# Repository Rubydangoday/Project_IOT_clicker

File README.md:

# Project_IOT_clicker — Hệ thống phản hồi lớp học dùng Remote nRF52840 (ARS)

Báo cáo môn học **IoT (IOTS337929)**, Nhóm 2, 
**ARS (Audience Response System)** là hệ thống hỏi–đáp trên lớp:
- Mỗi học sinh có một **Remote nRF52840** do nhóm tự thiết kế mạch.
- **Laptop giáo viên** vừa là máy chủ, vừa dùng Bluetooth sẵn có để thu đáp án, không cần thiết bị trung gian.
- Kết quả hiện ngay trên bảng điều khiển và màn chiếu, đồng thời được lưu lại để học sinh và phụ huynh xem trên web.
- Một **máy chủ Cloud 24/24** được laptop tự đồng bộ, để học sinh và phụ huynh dùng ở nhà.

📄 Báo cáo đầy đủ: [docs/bao-cao/Bao_cao_IOT_nhom2.docx](docs/bao-cao/Bao_cao_IOT_nhom2.docx)

---

## Cấu trúc thư mục

```
Project_IOT_clicker/
├── hardware/          Mạch Remote: dự án KiCad (sơ đồ nguyên lý, PCB 2 lớp 68×80 mm, thư viện ký hiệu/footprint,
│   ├── kicad/         Gerber prototype), bảng linh kiện BOM, ảnh sơ đồ và mạch in
│   ├── images/
│   └── BOM_linhkien_nhom2.xlsx
├── firmware/          Firmware Remote nRF52840 (Arduino, Adafruit nRF52 core 1.7.0)
│   └── ARS_remote_v3_17/   ← bản đang dùng (BLE advertising A6, LE 1M); các thư mục khác là phiên bản cũ / dự phòng GATT
├── server/            Phần mềm máy chủ phía Bluetooth (Python 3)
│   ├── bridge/        Bộ thu Bluetooth: ble_adv.py (đang dùng), adv_protocol.py, adv_phy.py (LE 1M); ble_gatt.py, ble_scan.py, bridge.py (dự phòng)
│   ├── ingest/        Bộ xử lý gói: ingest_adv.py (đang dùng), ingest.py (luật nghiệp vụ)
│   ├── common/        Đọc cấu hình, kết nối CSDL
│   └── history/       Bộ thu các phiên bản cũ
├── database/          MariaDB: schema.sql + migration 002–017
├── web/               Ứng dụng web PHP 8: cổng giáo viên, học sinh, phụ huynh, quản trị; API JSON; đồng bộ Cloud
├── deploy/            Cài đặt Ubuntu (install_ubuntu.sh, --cloud), dịch vụ systemd, nâng cấp/hoàn tác V3.16→V3.18, lệnh `ars`
├── tests/             Kiểm thử web (830 kiểm tra), giao thức quảng bá, LE 1M, firmware chạy giả lập trên máy tính
├── tools/             Đo 100 lần gửi, đo độ trễ, phân tích trace HCI, giả lập nhiều Remote
├── docs/              Tài liệu
│   ├── bao-cao/       Báo cáo môn học (Word)
│   ├── huong-dan-su-dung/  Hướng dẫn cho giáo viên, học sinh, phụ huynh, lập trình viên
│   ├── phien-ban/     Ghi chú từng phiên bản (START_HERE_*, UPGRADE_*, CHANGES_*), báo cáo hợp nhất V3.18 + Cloud
│   ├── HUONG_DAN_CAI_DAT.md · HUONG_DAN_CLOUD.md · HUONG_DAN_NGUOI_MOI.md · TONG_HOP_DU_AN.md
│   ├── KY_THUAT_CHI_TIET.md   Kiến trúc, luồng dữ liệu, giao thức (chi tiết kỹ thuật)
│   └── GATT_PROTOCOL_V3_11.md · BLUEZ_REQUIRED_CONFIG.md · ARS_BLE_Project_Handover.md
├── samples/           Đề thi mẫu (5 bộ × 20 câu: CSV/XLSX/DOCX), file mẫu nhập liệu
└── config.ini.example Cấu hình mẫu (DB, MQTT, Bluetooth)
```

## Kiến trúc

```
 TRÊN LỚP (laptop giáo viên, chạy offline)                                         Ở NHÀ (24/24)
 ┌──────────┐ BLE advertising ┌────────────────┐  MQTT  ┌────────────────┐  SQL  ┌─────────┐   tự đồng bộ   ┌───────────┐
 │ Remote   │ A6, LE 1M ─────▶│ Bộ thu BLE     │──────▶│ Bộ xử lý gói    │──────▶│ MariaDB │──── 3 phút ───▶│ ARS Cloud │◀── học sinh,
 │ nRF52840 │◀── STATE, KẾT QUẢ│ ble_adv.py     │◀──────│ ingest_adv.py   │◀──────│         │   (HTTPS JSON)  │ (Oracle + │    phụ huynh
 └──────────┘   (token 64 bit)└────────────────┘ Mosquitto└────────────────┘       └────▲────┘                 │ Tailscale)│
                                                                                       │                      └───────────┘
                                                              Web PHP (Apache) ────────┘ ◀── giáo viên, màn chiếu, học sinh, phụ huynh
```

Remote và bộ thu **chỉ truyền/nhận**. Mọi kiểm tra hợp lệ nằm ở bộ xử lý gói, nên muốn đổi luật chỉ cần sửa máy chủ, không phải nạp lại hàng chục Remote.

## Phần cứng Remote

Mạch 2 lớp 68×80 mm thiết kế bằng KiCad, gồm module nRF52840 SuperMini, bàn phím ma trận 14 phím, LED 7 đoạn 2 chữ số, đèn đỏ/xanh và nguồn 2 pin AA. File gốc nằm trong [hardware/kicad/](hardware/kicad/), Gerber trong [hardware/kicad/gerber_prototype/](hardware/kicad/gerber_prototype/), danh sách linh kiện trong [hardware/BOM_linhkien_nhom2.xlsx](hardware/BOM_linhkien_nhom2.xlsx).

**Sơ đồ nguyên lý**

| PCB mặt trên | PCB mặt dưới |
|:---:|:---:|
|  |  |

**Mạch thật đã lắp ráp** (Remote chạy bằng 2 pin AA, LED 7 đoạn đang hiển thị)

| | |
|:---:|:---:|
|  |  |

## Tính năng chính

| Khối | Tính năng |
|---|---|
| **Phần cứng** | Bo 2 lớp 68×80 mm; bàn phím ma trận 14 phím; LED 7 đoạn 2 số; đèn đỏ/xanh; 2 pin AA qua tăng áp, MOSFET chống ngược cực. Chi phí linh kiện ≈ 217.000 đ/Remote |
| **Firmware V3.17** | Nhập room/ID; điểm danh; chọn đáp án A–J; tự theo câu giáo viên đang chiếu, khoá khi câu đóng; tắt LED sau 30 giây; mỗi lần gửi là một giao dịch có token, gửi lại tối đa 6 lần |
| **Truyền không dây** | BLE advertising không kết nối (gói A6 21 byte), STATE/KẾT QUẢ ngược lại; laptop tắt Coded PHY để dùng LE 1M; đo 1 Remote: trung vị 597 ms, p95 1,17 s |
| **Máy chủ** | 10 bước kiểm tra kèm mã lý do từ chối; lưu kết quả giao dịch cùng đáp án trong một giao dịch CSDL (gửi lại không ghi trùng); tự đóng câu hết giờ |
| **Web giáo viên** | Lớp và danh sách học sinh (nhập Excel/CSV/Word/TXT); soạn câu từ Word/Excel/PDF/PowerPoint, công thức toán, trộn đề; bảng điều khiển và màn chiếu thời gian thực; **điểm danh tự động**; kết quả theo câu (p, D) và học sinh; xuất Excel/CSV; bài giảng; bài tập về nhà (AI gợi ý chấm); thi đua; **cấp tài khoản phụ huynh theo SĐT** |
| **Web học sinh** | Đăng nhập MSSV; ôn tập, sổ câu sai; bài tập về nhà (tệp, ảnh, ghi âm); bài giảng; thi đua; trợ lý học tập AI |
| **Web phụ huynh** | Đăng nhập bằng SĐT (bắt buộc đổi mật khẩu lần đầu) hoặc mã mời; **thông báo điểm danh và điểm sau mỗi buổi**; chuyên cần, tiến độ, kiến thức còn yếu, nhận xét |
| **Quản trị** | Giáo viên đăng ký trước, nhập mã mời sau (quản trị viên duyệt); trường và lớp hành chính; cấu hình AI, Zalo/SMS |
| **Cloud** | Máy chủ 24/24 (Oracle Cloud Always Free + Tailscale Funnel); laptop tự đồng bộ một chiều mỗi 3 phút, thử lại khi mất mạng |

## Công nghệ

- **Phần cứng:** nRF52840 SuperMini (ARM Cortex-M4F, BLE 5.0), KiCad.
- **Firmware:** Arduino C++, Adafruit nRF52 core (Bluefruit), SoftDevice, FreeRTOS.
- **Sóng:** BLE advertising, LE 1M PHY.
- **Bộ thu:** Python 3, bleak, dbus-fast, BlueZ / D-Bus, Bluetooth MGMT API.
- **Truyền tin nội bộ:** MQTT (Mosquitto, paho-mqtt, MQTT qua WebSocket).
- **CSDL:** MariaDB (InnoDB, VIEW).
- **Web:** PHP 8 (không framework), Apache, JavaScript thuần, KaTeX, mã QR, xuất Excel/Word, đọc PDF (poppler).
- **AI:** Anthropic Claude, Google Gemini, OpenAI, có chế độ Cơ bản không cần Internet.
- **Đăng nhập:** OAuth 2.0 Google.
- **Cloud và vận hành:** Oracle Cloud, Tailscale Funnel, Avahi mDNS, systemd, Ubuntu.
- **Kiểm thử:** Python unittest, requests, BeautifulSoup, g++.

## Cài đặt nhanh

**Laptop lớp học mới (Ubuntu 22.04 / 24.04)**
```bash
sudo bash deploy/install_ubuntu.sh                 # web, CSDL, MQTT, dịch vụ; mở http://ars.local/gv
# chuyển sang truyền quảng bá V3.18 (theo thứ tự, mỗi bước có sao lưu + hoàn tác):
sudo bash deploy/install_gatt.sh && sudo bash deploy/install_adv16.sh
sudo bash deploy/update_adv17.sh && sudo bash deploy/update_adv18.sh
```
Nạp firmware `firmware/ARS_remote_v3_17/ARS_remote_v3_17.ino` cho Remote (Arduino IDE, board Adafruit nRF52).

**Máy chủ Cloud** (Ubuntu, không cần Bluetooth): `sudo bash deploy/install_ubuntu.sh --cloud`, sau đó làm theo [docs/HUONG_DAN_CLOUD.md](docs/HUONG_DAN_CLOUD.md).

Hướng dẫn sử dụng: [docs/huong-dan-su-dung/](docs/huong-dan-su-dung/README.md) · Cài đặt chi tiết: [docs/HUONG_DAN_CAI_DAT.md](docs/HUONG_DAN_CAI_DAT.md) · Kỹ thuật: [docs/KY_THUAT_CHI_TIET.md](docs/KY_THUAT_CHI_TIET.md)

## Kiểm thử

| Hạng mục | Lệnh | Kết quả |
|---|---|---|
| Web, CSDL, đồng bộ Cloud (11 bộ, CSDL MariaDB tạm) | `bash tests/run_local.sh` | 830/830 đạt, 0 cảnh báo PHP |
| Giao thức quảng bá, bộ thu, bộ xử lý gói | `python3 tests/adv_unit.py` | 19/19 đạt |
| Cấu hình LE 1M, trace HCI | `python3 tests/adv18_unit.py` | 11/11 đạt |
| Firmware chạy giả lập trên máy tính | `bash tests/adv_firmware_host/run.sh` | Đạt |
| Remote thật trên PCB, LE 1M | `bash tools/test_adv18_100.sh` | 34/34 giao dịch có kết quả; trung vị 597 ms, p95 1.172 ms |

Giới hạn: mới đo thực tế với **một** Remote; tải vô tuyến khi cả lớp (khoảng 50 Remote) bấm cùng lúc chưa được đo.

## Nhóm thực hiện (Nhóm 2)

| Họ và tên | MSSV |
|---|---|
| Nguyễn Thị Ánh Ngọc | 23134040 |
| Lê Lữ Anh Khôi | 23134033 |
| Trần Trăng Sáng | 23134050 |
| Nguyễn Trung Tín | 23134055 |

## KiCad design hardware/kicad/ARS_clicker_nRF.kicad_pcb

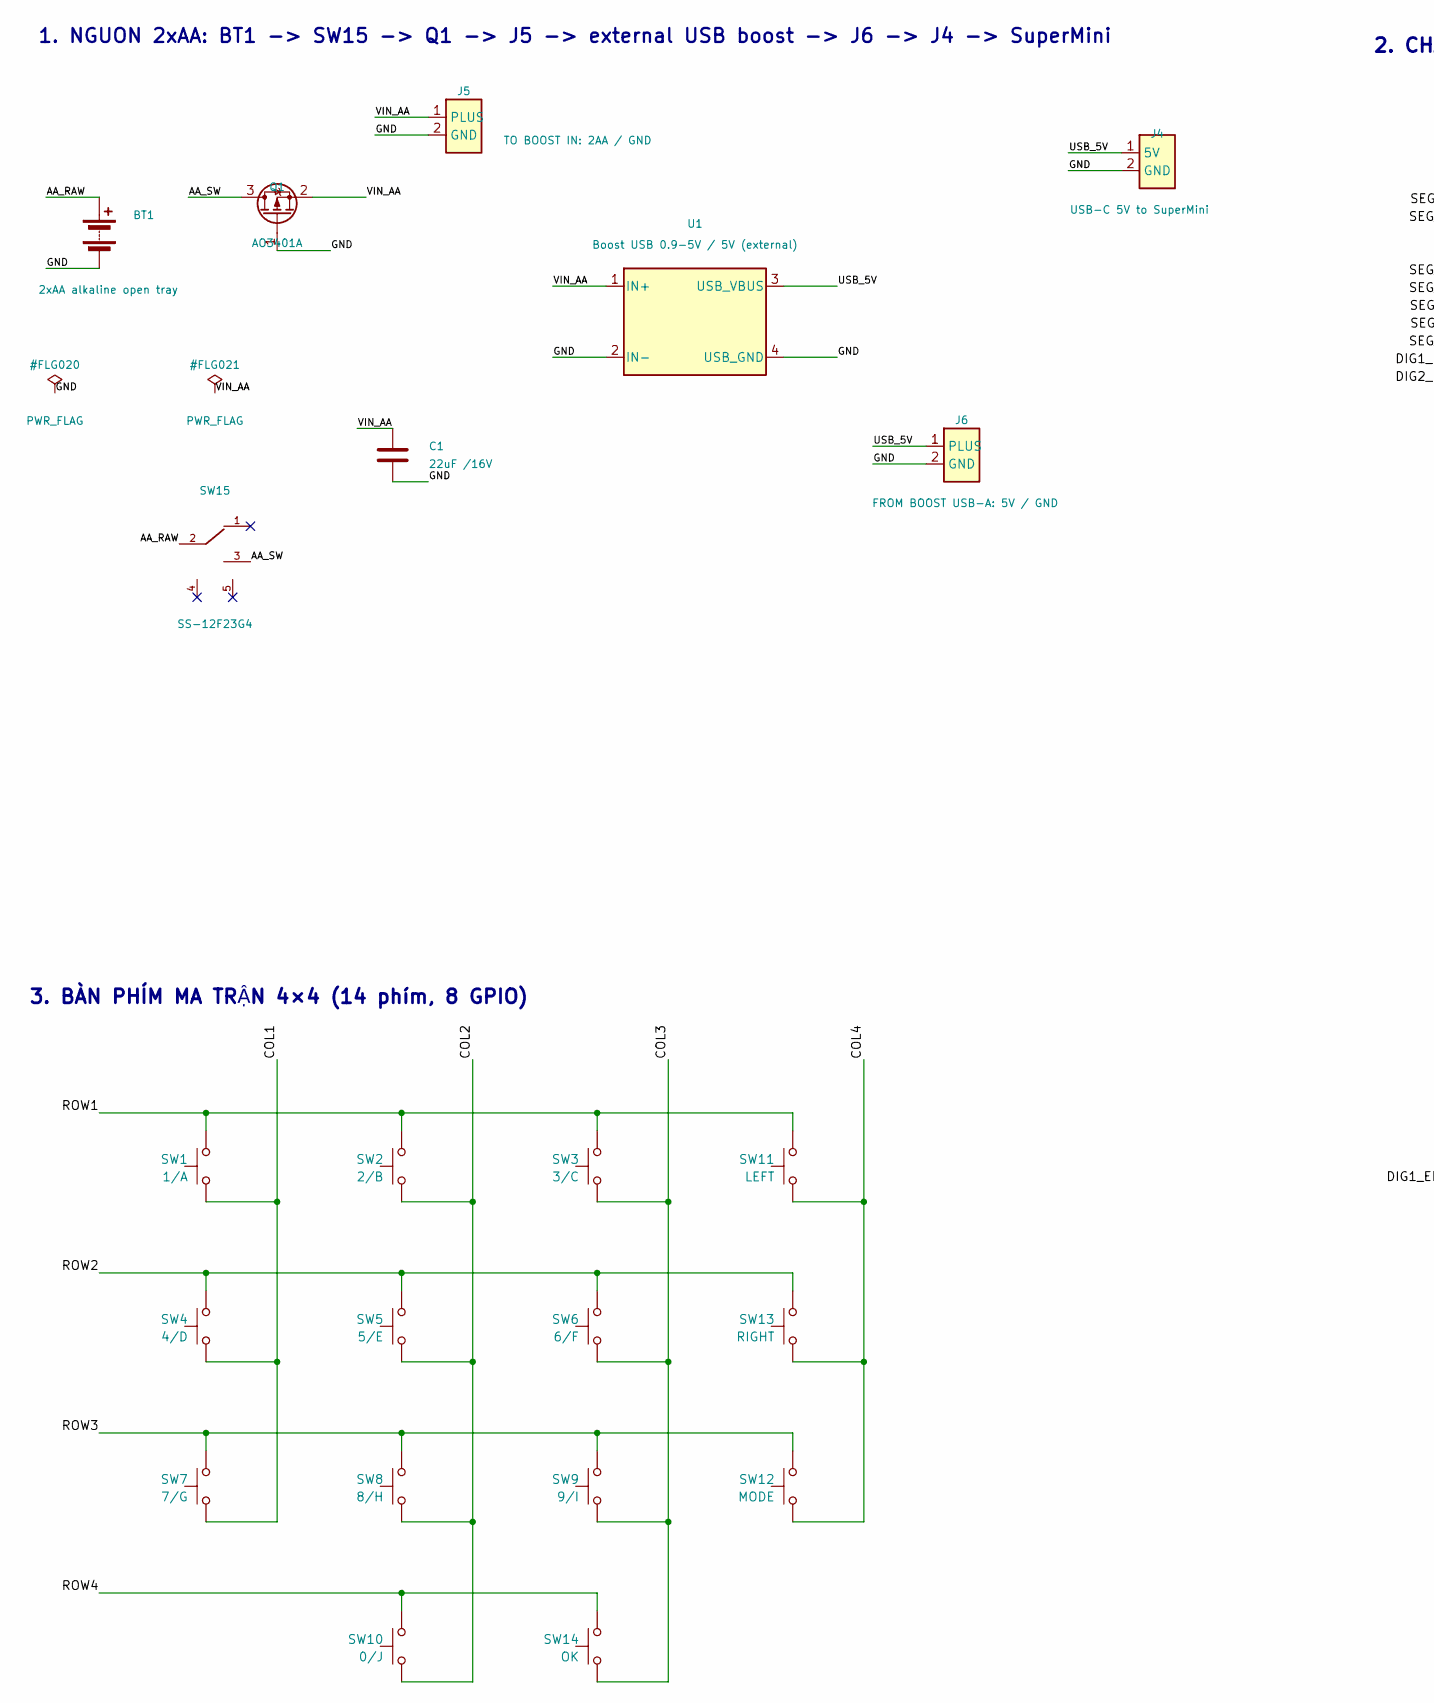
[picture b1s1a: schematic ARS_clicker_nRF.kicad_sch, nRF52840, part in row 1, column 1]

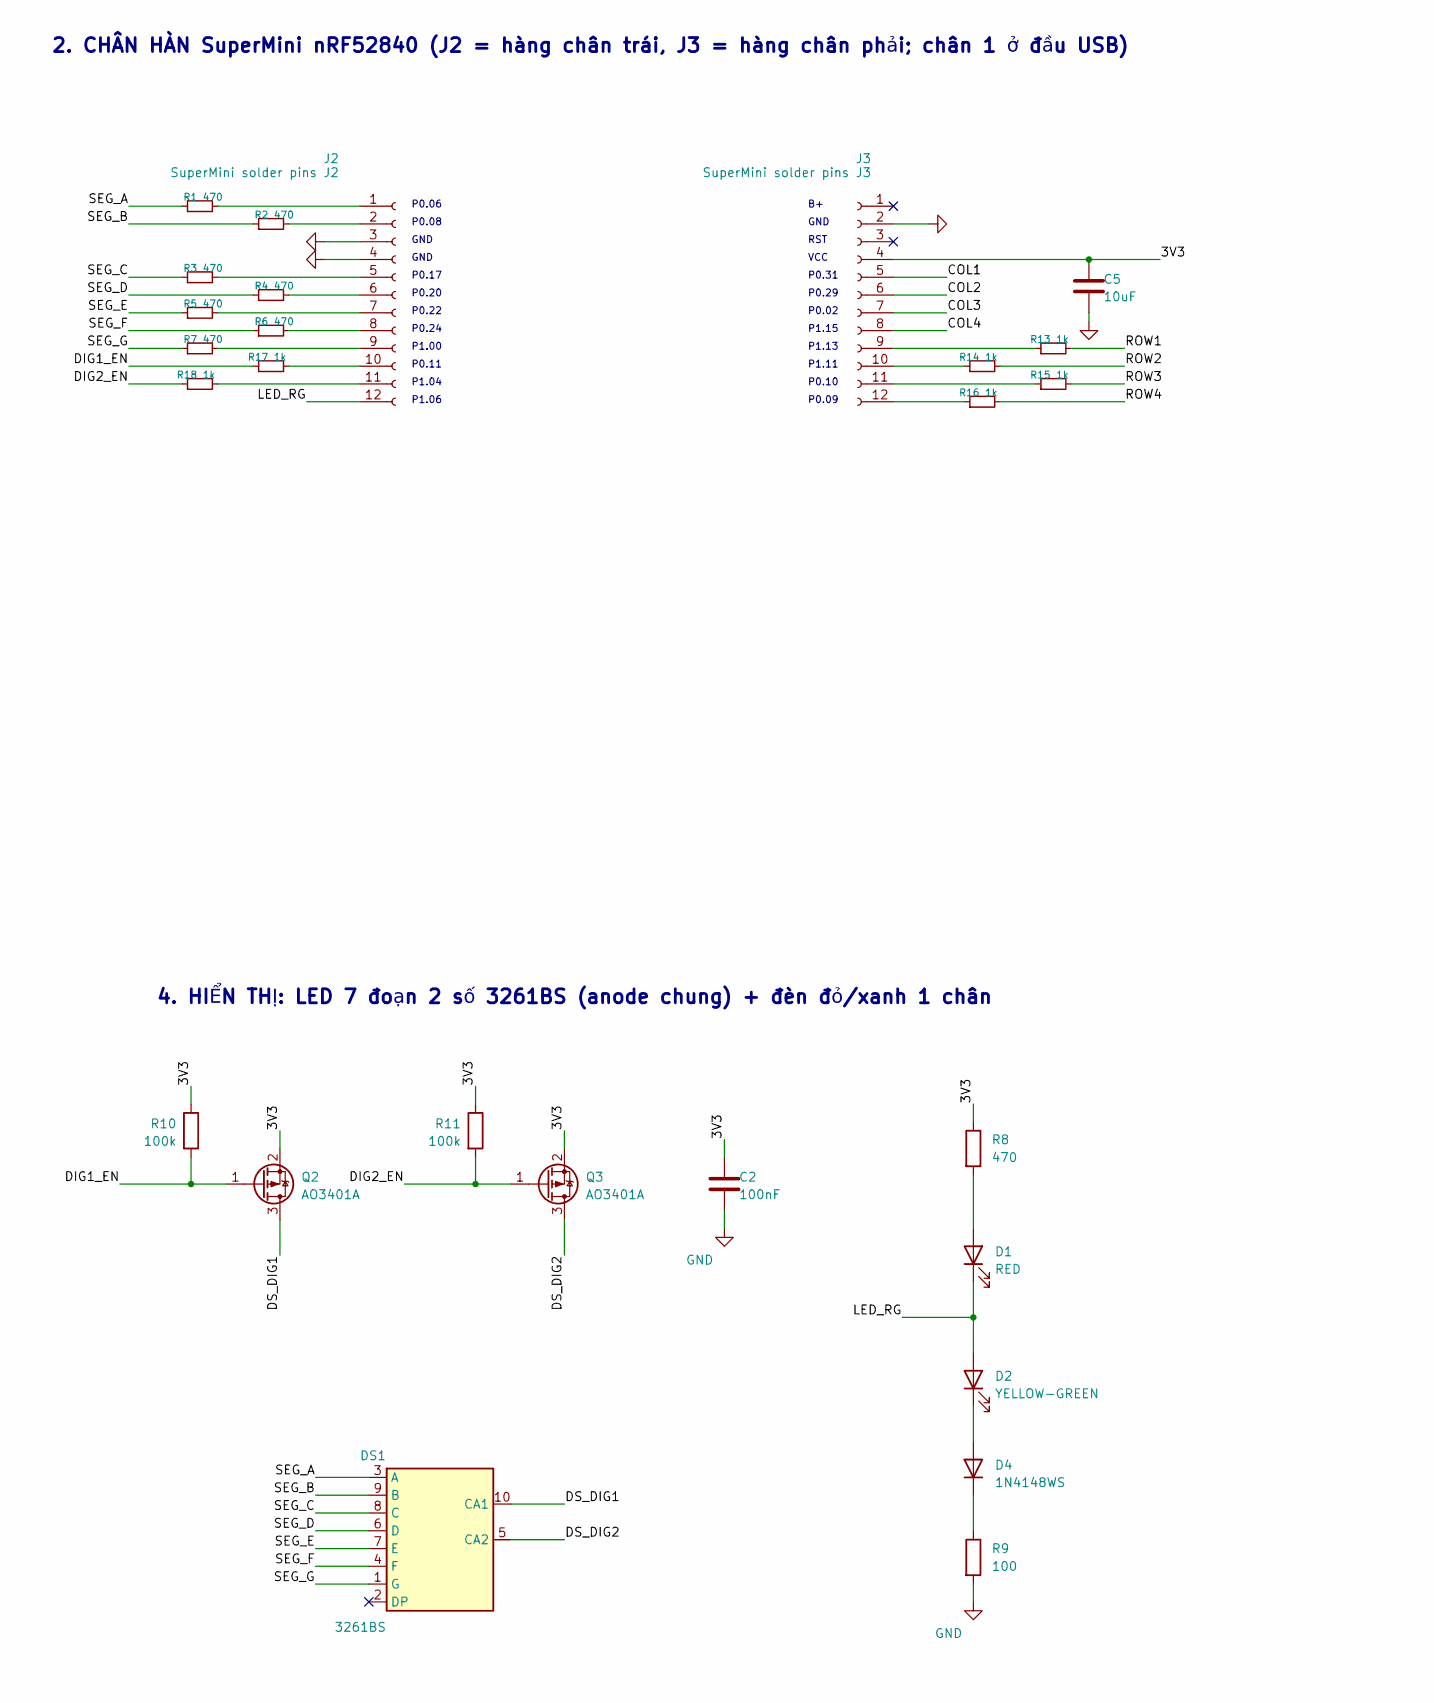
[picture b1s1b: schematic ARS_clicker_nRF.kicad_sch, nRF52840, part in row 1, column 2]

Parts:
BT1: 2xAA alkaline open tray; SolderWire-0.5sqmm_1x02_P4.6mm_D0.9mm_OD2.1mm
C1: 22uF /16V; C_1206_3216Metric
C2: 100nF; C_0603_1608Metric
C5: 10uF; C_0603_1608Metric
D1: RED; LED_0603_1608Metric
D2: YELLOW-GREEN; LED_0603_1608Metric
D4: 1N4148WS; D_SOD-323
DS1: 3261BS
J2: SuperMini solder pins J2; ModulePins_1x12_P2.54mm_Low
J3: SuperMini solder pins J3; ModulePins_1x12_P2.54mm_Low
J4: USB-C 5V to SuperMini; SolderWire-0.5sqmm_1x02_P4.6mm_D0.9mm_OD2.1mm
J5: TO BOOST IN: 2AA / GND; SolderWire-0.5sqmm_1x02_P4.6mm_D0.9mm_OD2.1mm
J6: FROM BOOST USB-A: 5V / GND; SolderWire-0.5sqmm_1x02_P4.6mm_D0.9mm_OD2.1mm
Q1, Q2, Q3: AO3401A; SOT-23
R1, R2, R3, R4, R5, R6, R7, R8: 470; R_0603_1608Metric
R9: 100; R_0603_1608Metric
R10, R11: 100k; R_0603_1608Metric
R13, R14, R15, R16, R17, R18: 1k; R_0603_1608Metric
SW1: 1/A; SW_IC3236_2pin_SMD_P6mm
SW2: 2/B; SW_IC3236_2pin_SMD_P6mm
SW3: 3/C; SW_IC3236_2pin_SMD_P6mm
SW4: 4/D; SW_IC3236_2pin_SMD_P6mm
SW5: 5/E; SW_IC3236_2pin_SMD_P6mm
SW6: 6/F; SW_IC3236_2pin_SMD_P6mm
SW7: 7/G; SW_IC3236_2pin_SMD_P6mm
SW8: 8/H; SW_IC3236_2pin_SMD_P6mm
SW9: 9/I; SW_IC3236_2pin_SMD_P6mm
SW10: 0/J; SW_IC3236_2pin_SMD_P6mm
SW11: LEFT; SW_IC3236_2pin_SMD_P6mm
SW12: MODE; SW_IC3236_2pin_SMD_P6mm
SW13: RIGHT; SW_IC3236_2pin_SMD_P6mm
SW14: OK; SW_IC3236_2pin_SMD_P6mm
SW15: SS-12F23G4; SW_SS12F23G4
U1: Boost USB 0.9-5V / 5V (external)

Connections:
/3V3: C2.1, C5.1, J3.4, Q2.2 (S), Q3.2 (S), R8.1, R10.1, R11.1
/AA_RAW: BT1.1 (+), SW15.2 (COM)
/AA_SW: Q1.3 (D), SW15.3 (ON)
/COL1: J3.5, SW1.1, SW4.1, SW7.1
/COL2: J3.6, SW2.1, SW5.1, SW8.1, SW10.1
/COL3: J3.7, SW3.1, SW6.1, SW9.1, SW14.1
/COL4: J3.8, SW11.1, SW12.1, SW13.1
/DIG1_EN: Q2.1 (G), R10.2, R17.1
/DIG2_EN: Q3.1 (G), R11.2, R18.1
/DS_DIG1: DS1.10 (CA1), Q2.3 (D)
/DS_DIG2: DS1.5 (CA2), Q3.3 (D)
/LED_RG: D1.1 (K), D2.2 (A), J2.12
/ROW1: R13.2, SW1.2, SW2.2, SW3.2, SW11.2
/ROW2: R14.2, SW4.2, SW5.2, SW6.2, SW13.2
/ROW3: R15.2, SW7.2, SW8.2, SW9.2, SW12.2
/ROW4: R16.2, SW10.2, SW14.2
/SEG_A: DS1.3 (A), R1.1
/SEG_B: DS1.9 (B), R2.1
/SEG_C: DS1.8 (C), R3.1
/SEG_D: DS1.6 (D), R4.1
/SEG_E: DS1.7 (E), R5.1
/SEG_F: DS1.4 (F), R6.1
/SEG_G: DS1.1 (G), R7.1
/USB_5V: J4.1 (5V), J6.1 (PLUS), U1.3 (USB_VBUS)
/VIN_AA: C1.1, J5.1 (PLUS), Q1.2 (S), U1.1 (IN+)
GND: BT1.2 (-), C1.2, C2.2, C5.2, J2.3, J2.4, J3.2, J4.2 (GND), J5.2 (GND), J6.2 (GND), Q1.1 (G), R9.2, U1.2 (IN-), U1.4 (USB_GND)
unnamed: D1.2 (A), R8.2
unnamed: D2.1 (K), D4.2 (A)
unnamed: D4.1 (K), R9.1
unnamed: J2.1, R1.2
unnamed: J2.2, R2.2
unnamed: J2.5, R3.2
unnamed: J2.6, R4.2
unnamed: J2.7, R5.2
unnamed: J2.8, R6.2
unnamed: J2.9, R7.2
unnamed: J2.10, R17.2
unnamed: J2.11, R18.2
unnamed: J3.9, R13.1
unnamed: J3.10, R14.1
unnamed: J3.11, R15.1
unnamed: J3.12, R16.1

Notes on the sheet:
VCC
P0.29
P1.06
3. BÀN PHÍM MA TRẬN 4×4 (14 phím, 8 GPIO)
P0.17
GND
P1.15
RST
P0.10
P1.13
P0.06
P0.31
P0.20
P0.24
4. HIỂN THỊ: LED 7 đoạn 2 số 3261BS (anode chung) + đèn đỏ/xanh 1 chân
P0.09
P0.22
P1.04
2. CHÂN HÀN SuperMini nRF52840 (J2 = hàng chân trái, J3 = hàng chân phải; chân 1 ở đầu USB)
P0.11
P1.00
P0.08
P0.02
P1.11
1. NGUON 2xAA: BT1 -> SW15 -> Q1 -> J5 -> external USB boost -> J6 -> J4 -> SuperMini

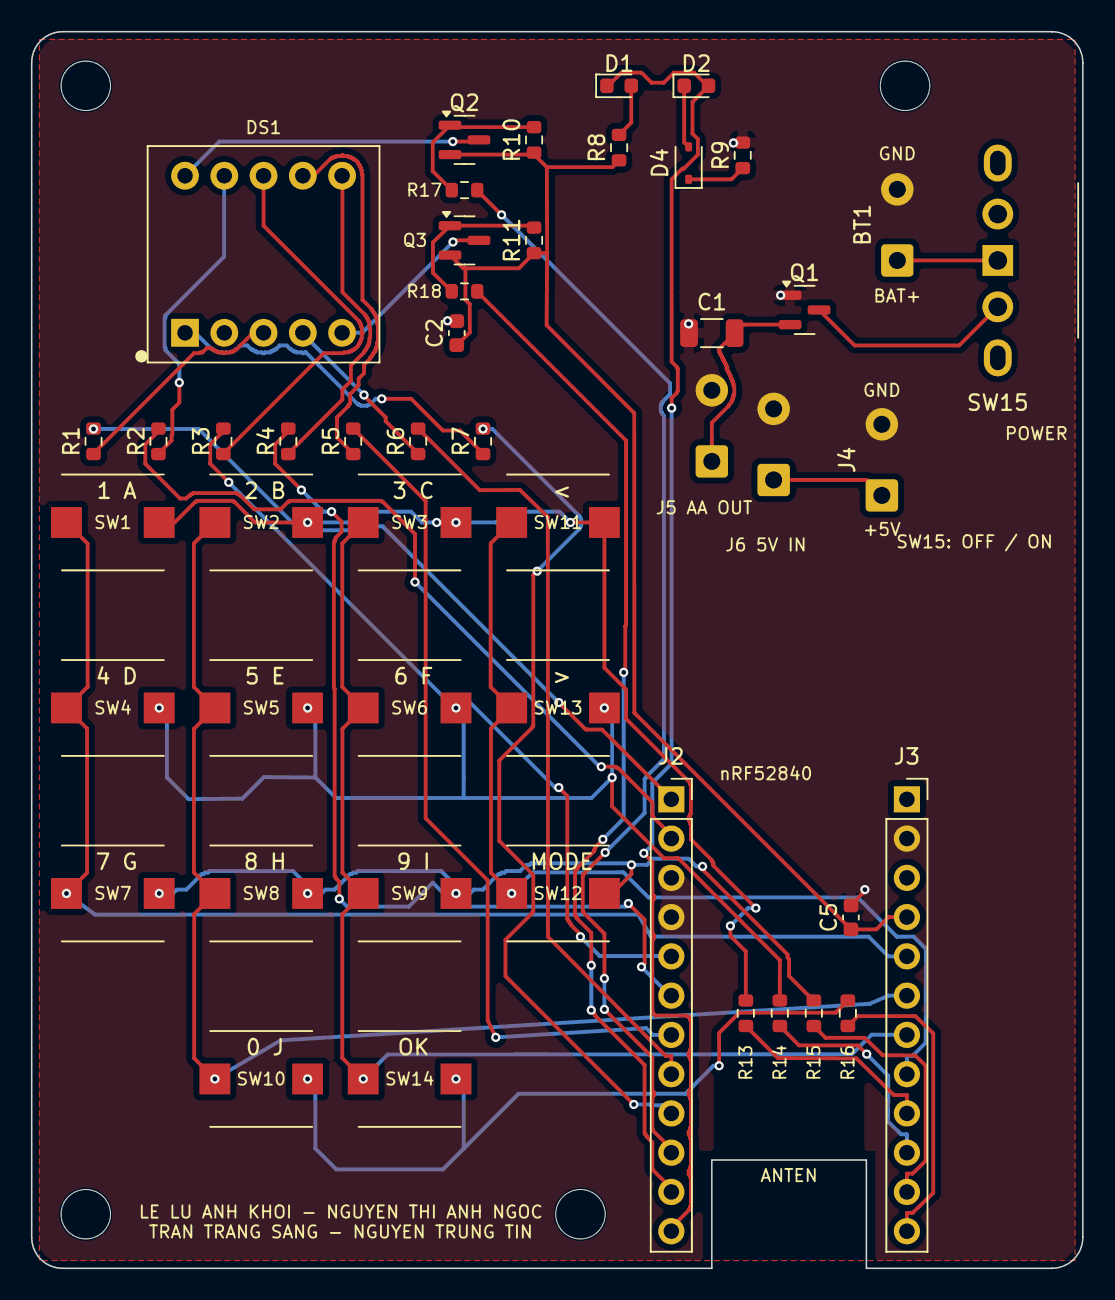
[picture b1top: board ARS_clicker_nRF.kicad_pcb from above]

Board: 2 copper layers, 68.0 x 80.0 mm, 52 parts (0 on the bottom side), 42 nets.

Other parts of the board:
H1, H2, H3, H4: MountingHole_3.2mm_M3

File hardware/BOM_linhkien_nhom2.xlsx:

STT | Tên linh kiện | Ký hiệu | Số lượng | Đơn giá (VNĐ) | Thành tiền (VNĐ)
1 | SuperMini nRF52840 | — | 1 | 115000 | 115000
2 | Header đực thẳng 1×40, 2,54mm | J2, J3 | 24 | 25 | 600
3 | Module tăng áp | U1 | 1 | 10000 | 10000
4 | Dây USB-A | J6 + J5 | 1 | 26220 | 26220
5 | Khay hở 2×AA có dây, IC2410 | BT1 | 1 | 3420 | 3420
6 | Voniko alkaline AA LR6 2PK, 1,5 V, vỉ 2 viên | — | 2 | 9800 | 19600
7 | Tụ điện 22 µF 16 V 1206 | C1 | 1 | 700 | 700
8 | Tụ điện 100 nF 50 V 0603 | C2 | 1 | 200 | 200
9 | MOSFET P AO3401 | Q1, Q2, Q3 | 3 | 500 | 1500
10 | LED đôi 7 đoạn 3261BS, anode chung | DS1 | 1 | 5000 | 5000
11 | LED đỏ | D1 | 1 | 200 | 200
12 | LED green | D2 | 1 | 300 | 300
13 | Nút 2 chân SMD IC3236 | SW1–SW14 | 14 | 1710 | 23940
14 | Điện trở 1K 0603 1 % | R13–R18 | 6 | 40 | 240
15 | Điện trở 470R 0603 1 % | R1–R8 | 8 | 40 | 320
16 | Diode 1N4148WS SOD-323 | D4 | 1 | 200 | 200
17 | Điện trở 100K 0603 1 % | R10, R11 | 2 | 40 | 80
18 | Tụ điện 10 µF 25 V 0603 | C5 | 1 | 400 | 400
19 | Điện trở 100R 0603 1 % | R9 | 1 | 40 | 40
22 | Dây USB-C | J4 | 1 | 7980 | 7980
23 | Công tắc gạt ngang | SW15 | 1 | 855 | 855
 | TỔNG CỘNG |  |  |  | 216795

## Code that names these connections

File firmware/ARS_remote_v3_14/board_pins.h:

#pragma once

#include <stdint.h>
#include <nrf_gpio.h>

namespace BoardPins {

// ===== Power control on SuperMini / nice!nano style board =====
static constexpr uint32_t EXT_VCC = NRF_GPIO_PIN_MAP(0, 13); // P0.13

// ===== 7-segment DS1: common anode =====
static constexpr uint32_t SEG_A = NRF_GPIO_PIN_MAP(0, 6);   // P0.06
static constexpr uint32_t SEG_B = NRF_GPIO_PIN_MAP(0, 8);   // P0.08
static constexpr uint32_t SEG_C = NRF_GPIO_PIN_MAP(0, 17);  // P0.17
static constexpr uint32_t SEG_D = NRF_GPIO_PIN_MAP(0, 20);  // P0.20
static constexpr uint32_t SEG_E = NRF_GPIO_PIN_MAP(0, 22);  // P0.22
static constexpr uint32_t SEG_F = NRF_GPIO_PIN_MAP(0, 24);  // P0.24
static constexpr uint32_t SEG_G = NRF_GPIO_PIN_MAP(1, 0);   // P1.00

// Digit P-MOS gate control: LOW = digit ON
static constexpr uint32_t DIGIT_1 = NRF_GPIO_PIN_MAP(0, 11); // P0.11
static constexpr uint32_t DIGIT_2 = NRF_GPIO_PIN_MAP(1, 4);  // P1.04

// ===== Red/Green status LED =====
// RevJ assumption: LOW = RED, HIGH = GREEN, Hi-Z = OFF
static constexpr uint32_t STATUS_LED = NRF_GPIO_PIN_MAP(1, 6); // P1.06

// ===== Key matrix rows =====
static constexpr uint32_t ROW_1 = NRF_GPIO_PIN_MAP(1, 13); // P1.13
static constexpr uint32_t ROW_2 = NRF_GPIO_PIN_MAP(1, 11); // P1.11
static constexpr uint32_t ROW_3 = NRF_GPIO_PIN_MAP(0, 10); // P0.10 / NFC2
static constexpr uint32_t ROW_4 = NRF_GPIO_PIN_MAP(0, 9);  // P0.09 / NFC1

// ===== Key matrix columns =====
static constexpr uint32_t COL_1 = NRF_GPIO_PIN_MAP(0, 31); // P0.31
static constexpr uint32_t COL_2 = NRF_GPIO_PIN_MAP(0, 29); // P0.29
static constexpr uint32_t COL_3 = NRF_GPIO_PIN_MAP(0, 2);  // P0.02
static constexpr uint32_t COL_4 = NRF_GPIO_PIN_MAP(1, 15); // P1.15

}
